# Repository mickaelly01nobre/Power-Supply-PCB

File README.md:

# Power Supply PCB Project

This project involves the development of a power supply PCB that takes a 12V input and distributes 5V and 3.3V outputs, supporting up to 5A of current. The PCB features voltage regulators, a switching circuit with a MOSFET, energy monitoring, and motor overload protection.

## Key Components

- **LM805 (5V Regulator):** Provides a regulated 5V output from the 12V input.
- **LM1117 (3.3V Regulator):** Provides a regulated 3.3V output, powered by the 5V output from the LM805 in a **cascaded configuration**.
- **Electrolytic Capacitors (100uF):** Placed at the input of the regulators to filter low-frequency noise generated by motors in the system.
- **Ceramic Capacitors (100nF):** Placed at the output of the regulators to filter low-frequency noise caused by the switching circuit.
- **Electrolytic Capacitor (10uF):** Connected in parallel with the 12V power source to filter high- and low-frequency noise, ensuring a stable power supply.
- **MOSFET IRF9540N (P-Channel):** Used to control system power switching.
- **INA219 (Power Monitor):** A current/voltage sensor to monitor the system's energy consumption.
- **5A Fuse:** Protects the motors from overcurrent.
- **Diode (in parallel with the motors):** Protects the system from voltage spikes generated by the motors during shutdown.

## Functionality

This PCB receives a 12V input and distributes two regulated output voltages: 5V and 3.3V. Key functionalities include:

### 1. Voltage Regulation

- The LM805 regulates the 12V input to provide a 5V output.
- The LM1117 regulates the 5V output from the LM805 to provide a 3.3V output in a **cascaded configuration**.

### 2. Noise Filtering

- Electrolytic capacitors (100uF) filter low-frequency noise at the input of the regulators.
- Ceramic capacitors (100nF) filter noise at the output of the regulators caused by switching circuits.
- An electrolytic capacitor (10uF) connected in parallel with the 12V power source filters high- and low-frequency noise, providing a cleaner power supply.

### 3. Switching Circuit

- A P-Channel MOSFET (IRF9540N) is used to control system power.
- Two switches are included for power control:
  - **Emergency Stop Switch:** Connected to the gate of the MOSFET, this switch cuts power to the entire system when pressed.
  - **Power-On Switch:** Connected to the source of the MOSFET, this switch activates the system when pressed.

### 4. Energy Monitoring

- The INA219 sensor monitors the system's energy consumption, measuring both current and voltage.

### 5. Motor Overload Protection

- A 5A fuse in series with the motors prevents overcurrent damage.
- A diode in parallel with the motors protects against voltage spikes generated when the motors are powered off.

## Schematic

## PCB Layout

## Assembly Instructions

1. **Power Input:**
   - Connect a 12V input to the PCB's power input terminals.

2. **Voltage Regulators:**
   - The LM805 outputs 5V, which powers the LM1117 in a cascaded configuration to produce the 3.3V output.

3. **Switching Circuit:**
   - Connect the MOSFET as per the schematic, with the emergency stop switch wired to the gate and the power-on switch wired to the source.

4. **Energy Monitoring:**
   - Connect the INA219 sensor to measure current and voltage across the system.

5. **Motor Protection:**
   - Install the 5A fuse in series with the motors and the protection diode in parallel with the motors.

## Final Considerations

This project provides a robust solution for distributing 5V and 3.3V regulated outputs from a 12V input, featuring noise filtering, energy monitoring, and motor protection. The cascaded regulator configuration ensures efficient voltage regulation for sensitive components, while the additional 10uF capacitor improves noise filtering, ensuring a stable and reliable power supply. The system is ideal for applications involving motors and other components requiring a secure and clean power distribution.

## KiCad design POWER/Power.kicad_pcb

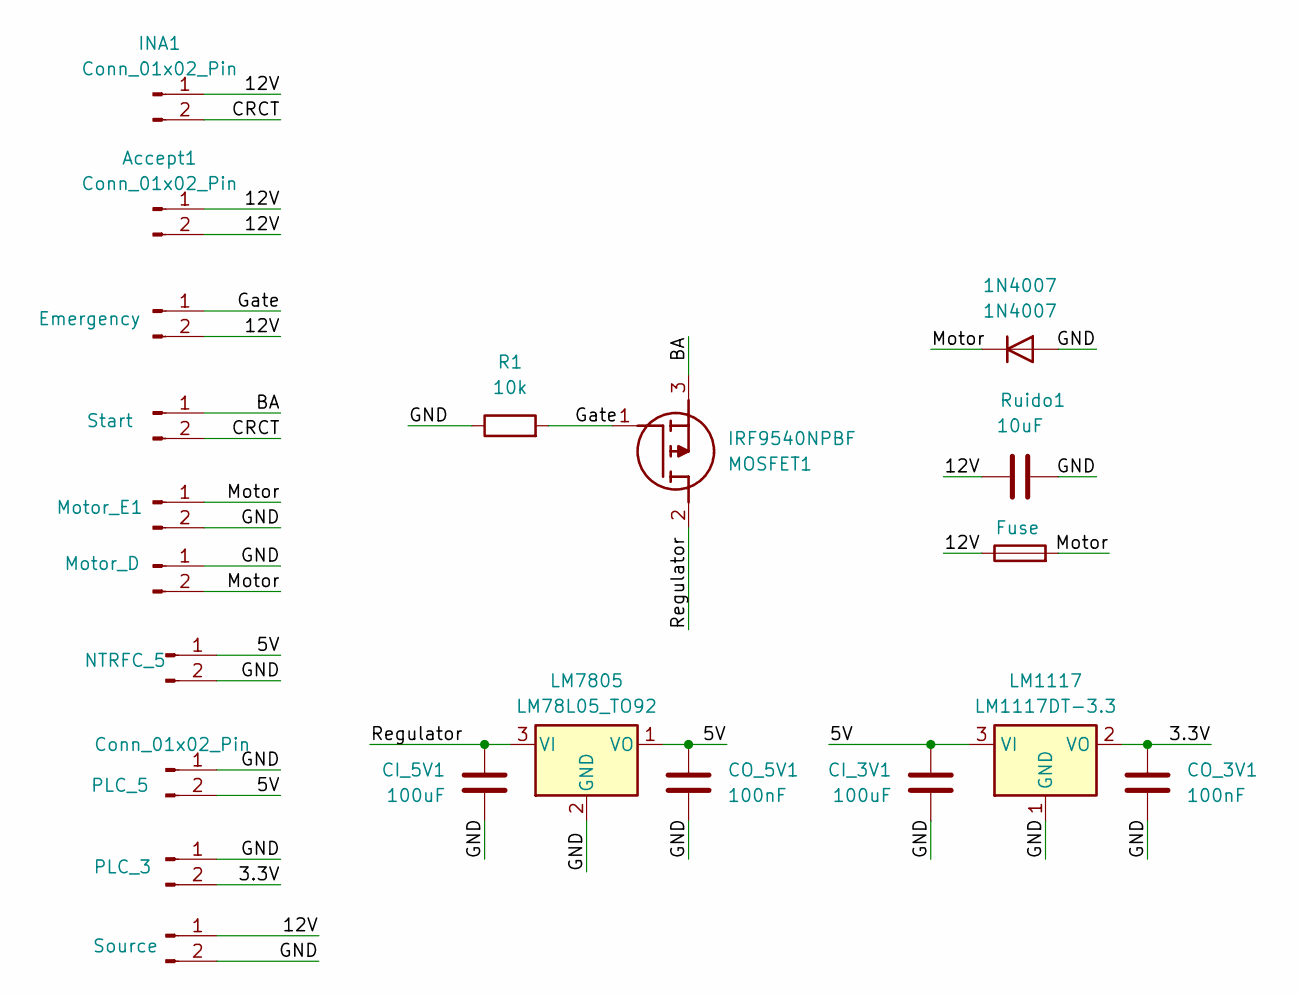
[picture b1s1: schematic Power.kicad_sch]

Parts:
1N4007: 1N4007; D_DO-41_SOD81_P10.16mm_Horizontal
Accept1: Conn_01x02_Pin; JST_VH_B2P-VH_1x02_P3.96mm_Vertical
CI_3V1, CI_5V1: 100uF; C_Radial_D6.3mm_H11.0mm_P2.50mm
CO_3V1, CO_5V1: 100nF; C_Disc_D3.0mm_W1.6mm_P2.50mm
F1: Fuse; Fuse_Littelfuse_372_D8.50mm
INA1: Conn_01x02_Pin; JST_VH_B2P-VH_1x02_P3.96mm_Vertical
J1: Emergency; JST_VH_B2P-VH_1x02_P3.96mm_Vertical
J2: Start; JST_VH_B2P-VH_1x02_P3.96mm_Vertical
J3: Motor_D; JST_VH_B2P-VH_1x02_P3.96mm_Vertical
J6: Source; JST_VH_B2P-VH_1x02_P3.96mm_Vertical
LM1117: LM1117DT-3.3; TO-92_Inline
LM7805: LM78L05_TO92; TO-92_Inline
MOSFET1: IRF9540NPBF; TO254P469X1042X1967-3P; Mouser Part Number 942-IRF9540NPBF
Motor_E1: Conn_01x02_Pin; JST_VH_B2P-VH_1x02_P3.96mm_Vertical
NTRFC_5: Conn_01x02_Pin; JST_XH_B2B-XH-A_1x02_P2.50mm_Vertical
PLC_3, PLC_5: Conn_01x02_Pin; JST_XH_B2B-XH-A_1x02_P2.50mm_Vertical
R1: 10k; R_Axial_DIN0204_L3.6mm_D1.6mm_P1.90mm_Vertical
Ruido1: 10uF; C_Radial_D5.0mm_H11.0mm_P2.00mm

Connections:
/3.3V: CO_3V1.1, LM1117.2 (VO), PLC_3.2
/5V: CI_3V1.1, CO_5V1.1, LM1117.3 (VI), LM7805.1 (VO), NTRFC_5.1, PLC_5.2
/12V: Accept1.1, Accept1.2, F1.1, INA1.1, J1.2, J6.1, Ruido1.2
/BA: J2.1, MOSFET1.3 (S)
/CRCT: INA1.2, J2.2
/GND: 1N4007.2 (A), CI_3V1.2, CI_5V1.2, CO_3V1.2, CO_5V1.2, J3.1, J6.2, LM1117.1 (GND), LM7805.2 (GND), Motor_E1.2, NTRFC_5.2, PLC_3.1, PLC_5.1, R1.1, Ruido1.1
/Gate: J1.1, MOSFET1.1 (G), R1.2
/Motor: 1N4007.1 (K), F1.2, J3.2, Motor_E1.1
/Regulator: CI_5V1.1, LM7805.3 (VI), MOSFET1.2 (D)

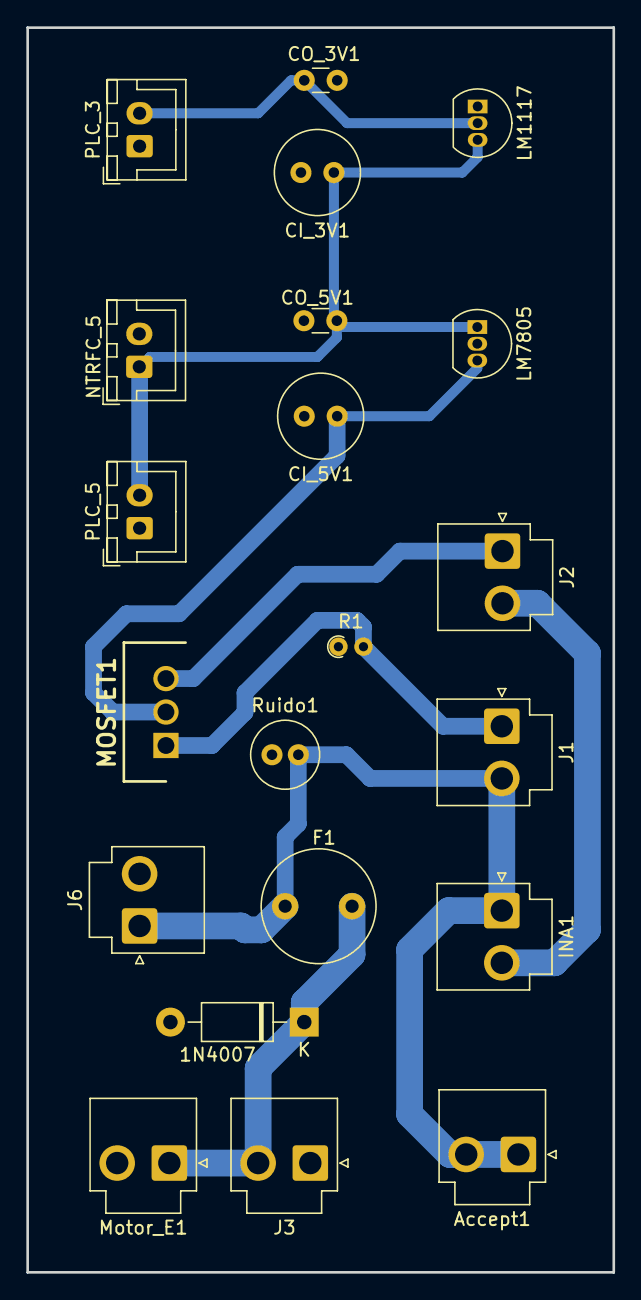
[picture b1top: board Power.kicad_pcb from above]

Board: 2 copper layers, 44.5 x 94.5 mm, 21 parts (0 on the bottom side), 9 nets.
